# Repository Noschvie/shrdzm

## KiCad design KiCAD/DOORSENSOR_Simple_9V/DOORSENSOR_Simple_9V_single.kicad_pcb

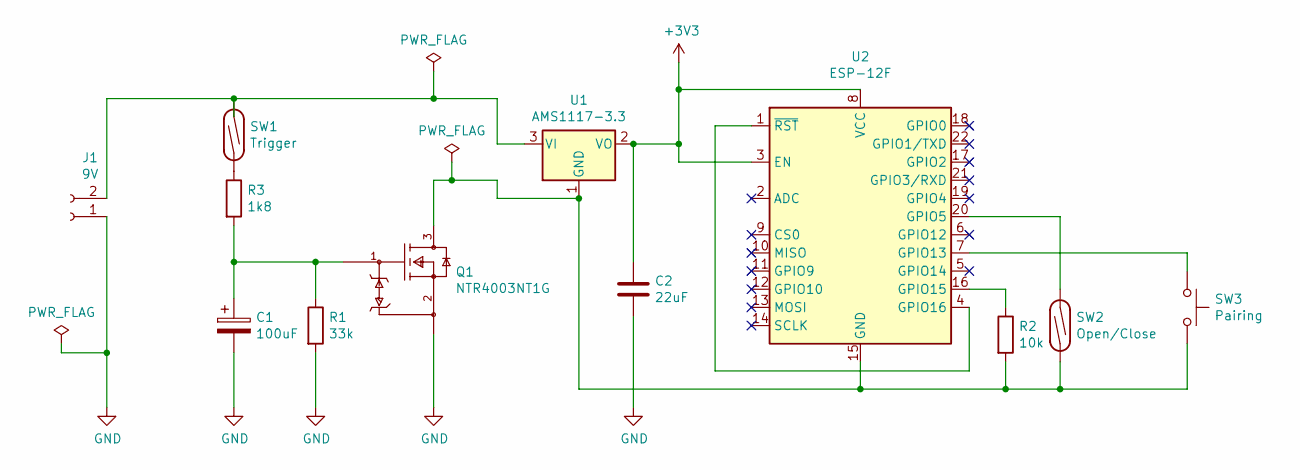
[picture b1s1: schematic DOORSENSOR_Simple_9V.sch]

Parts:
C1: 100uF; CP_Radial_D5.0mm_P2.50mm
C2: 22uF; C_1206_3216Metric_Pad1.33x1.80mm_HandSolder
J1: 9V; JST_PH_S2B-PH-K_1x02_P2.00mm_Horizontal
Q1: NTR4003NT1G; SOT-23; mouser part number 863-NTR4003NT1G; digikey description MOSFET N-CH 30V 500MA SOT-23
R1: 33k; R_0805_2012Metric_Pad1.20x1.40mm_HandSolder
R2: 10k; R_0805_2012Metric_Pad1.20x1.40mm_HandSolder
R3: 1k8; R_0805_2012Metric_Pad1.20x1.40mm_HandSolder
SW1: Trigger; Magnetic Reed Relay
SW2: Open/Close; Magnetic Reed Relay
SW3: Pairing; SW_SPST_CK_RS282G05A3
U1: AMS1117-3.3; SOT-223-3_TabPin2
U2: ESP-12F; ESP-12E

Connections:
+3V3: C2.1, U1.2 (VO), U2.3 (EN), U2.8 (VCC)
GND: C1.2, C2.2, J1.1, Q1.2 (S), R1.2
unnamed: C1.1, Q1.1 (G), R1.1, R3.2
unnamed: J1.2, SW1.1, U1.3 (VI)
unnamed: Q1.3 (D), R2.2, SW2.2, SW3.2, U1.1 (GND), U2.15 (GND)
unnamed: R2.1, U2.16 (GPIO15)
unnamed: R3.1, SW1.2
unnamed: SW2.1, U2.20 (GPIO5)
unnamed: SW3.1, U2.7 (GPIO13)
unnamed: U2.1 (~RST), U2.4 (GPIO16)

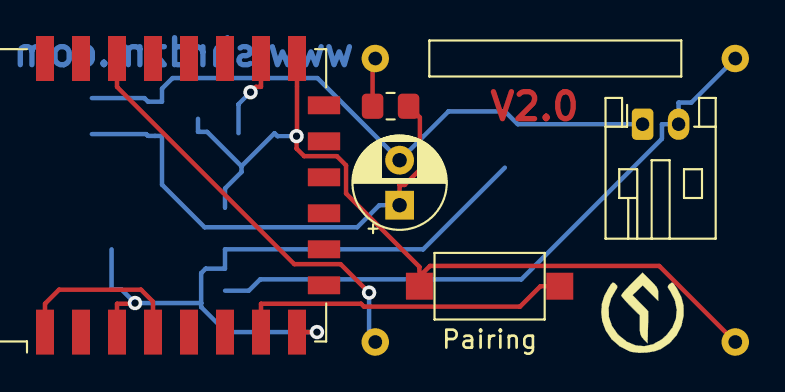
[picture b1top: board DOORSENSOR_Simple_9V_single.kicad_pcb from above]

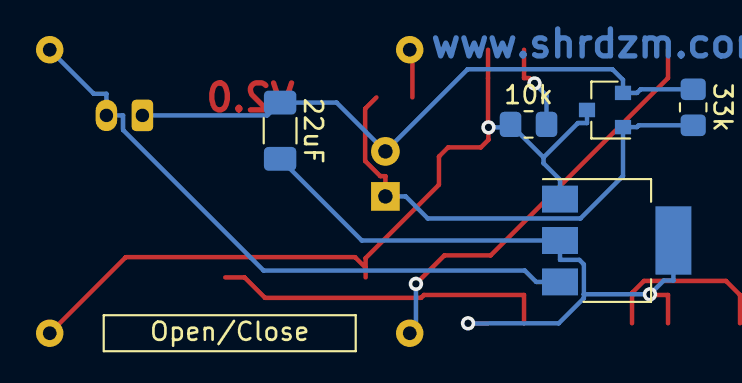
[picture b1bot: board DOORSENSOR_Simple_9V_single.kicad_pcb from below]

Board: 2 copper layers, 14 parts (7 on the bottom side), 10 nets.

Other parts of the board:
G1: LOGO; SHRDZM Symbol 5x5
G2: LOGO; SHRDZM 12x4

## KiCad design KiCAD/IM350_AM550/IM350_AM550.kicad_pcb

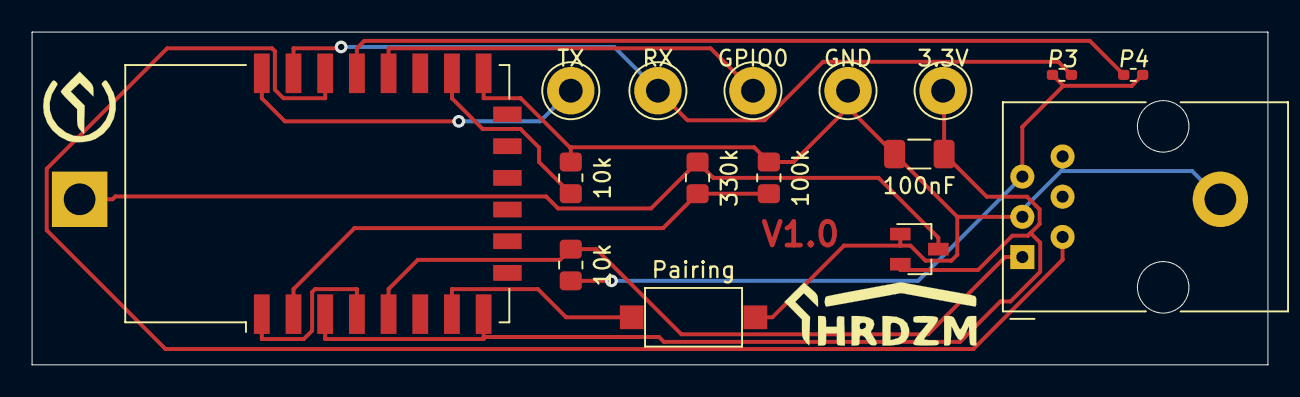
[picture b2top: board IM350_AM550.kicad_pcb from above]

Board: 2 copper layers, 78.0 x 21.0 mm, 19 parts (1 on the bottom side), 14 nets.

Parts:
BT1: Battery_Cell; BatteryHolder_MPD_BH-18650-PC2_NoHole
C2: 100nF; C_1206_3216Metric_Pad1.33x1.80mm_HandSolder
G1: LOGO; SHRDZM 12x4
G2: LOGO; SHRDZM Symbol 5x5
J1: 3.3V; Pin_D1.3mm_L11.0mm_LooseFit
J2: TX; Pin_D1.3mm_L11.0mm_LooseFit
J3: RX; Pin_D1.3mm_L11.0mm_LooseFit
J4: GPIO0; Pin_D1.3mm_L11.0mm_LooseFit
J6: GND; Pin_D1.3mm_L11.0mm_LooseFit
J7: RJ12; RJ12_Amphenol_54601
R1: 330k; R_0805_2012Metric_Pad1.20x1.40mm_HandSolder
R2: 100k; R_0805_2012Metric_Pad1.20x1.40mm_HandSolder
R3, R6: 0R; R_0402_1005Metric_Pad0.72x0.64mm_HandSolder
R4, R5: 10k; R_0805_2012Metric_Pad1.20x1.40mm_HandSolder
SW1: Pairing; SW_SPST_CK_RS282G05A3
U1: MCP1700-3302E_SOT23; SOT-23_Handsoldering
U2: ESP-12F; ESP-12E

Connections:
+3V3: C2.1, J1.1, U1.2, U2.3, U2.8
+3V8: BT1.1, R1.1, U1.3
/GPIO3: J3.1, R3.2, U2.21
/GPIO4: R6.2, U2.19
GND: BT1.2, C2.2, J6.1, J7.3, J7.6, R2.2, R4.2, SW1.2, U1.1, U2.15
unnamed: J2.1, U2.22
unnamed: J4.1, U2.18
unnamed: J7.1, R5.1, U2.5
unnamed: J7.2, U2.20
unnamed: J7.5, R3.1, R5.2, R6.1
unnamed: R1.2, R2.1, U2.2
unnamed: R4.1, U2.16
unnamed: SW1.1, U2.7
unnamed: U2.1, U2.4

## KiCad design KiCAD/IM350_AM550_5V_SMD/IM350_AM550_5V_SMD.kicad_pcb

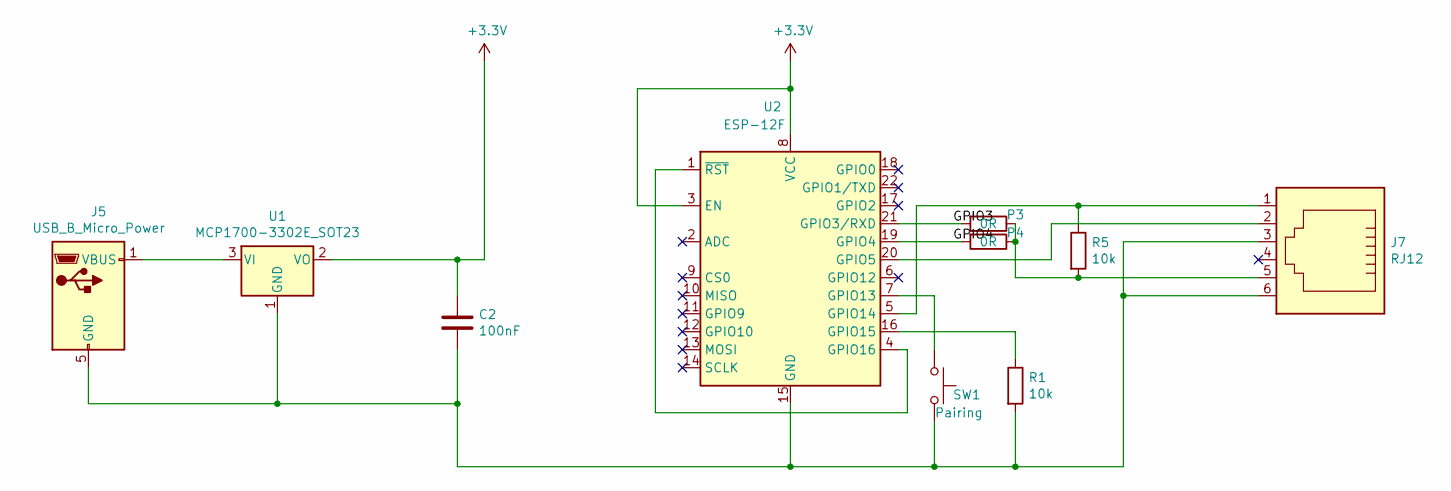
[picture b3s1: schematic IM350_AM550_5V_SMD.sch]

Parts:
C2: 100nF; C_1206_3216Metric_Pad1.33x1.80mm_HandSolder
J5: USB_B_Micro_Power; USB_Micro-B_Power
J7: RJ12; RJ12_Amphenol_54601_Reduced
P3, P4: 0R; R_0402_1005Metric_Pad0.72x0.64mm_HandSolder
R1, R5: 10k; R_0805_2012Metric_Pad1.20x1.40mm_HandSolder
SW1: Pairing; SW_SPST_CK_RS282G05A3
U1: MCP1700-3302E_SOT23; SOT-23_Handsoldering
U2: ESP-12F; ESP-12E

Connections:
+3V3: C2.1, U1.2 (VO), U2.3 (EN), U2.8 (VCC)
/GPIO3: P3.2, U2.21 (GPIO3/RXD)
/GPIO4: P4.2, U2.19 (GPIO4)
unnamed: C2.2, J5.5 (GND), J7.3, J7.6, R1.2, SW1.2, U1.1 (GND), U2.15 (GND)
unnamed: J5.1 (VBUS), U1.3 (VI)
unnamed: J7.1, R5.1, U2.5 (GPIO14)
unnamed: J7.2, U2.20 (GPIO5)
unnamed: J7.5, P3.1, P4.1, R5.2
unnamed: R1.1, U2.16 (GPIO15)
unnamed: SW1.1, U2.7 (GPIO13)
unnamed: U2.1 (~RST), U2.4 (GPIO16)

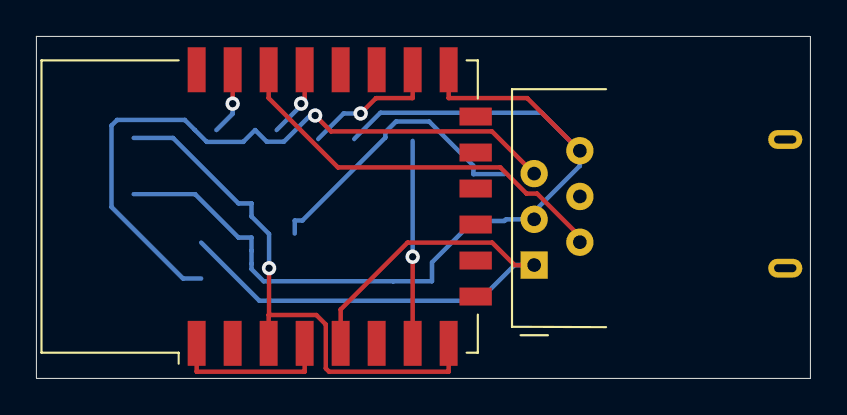
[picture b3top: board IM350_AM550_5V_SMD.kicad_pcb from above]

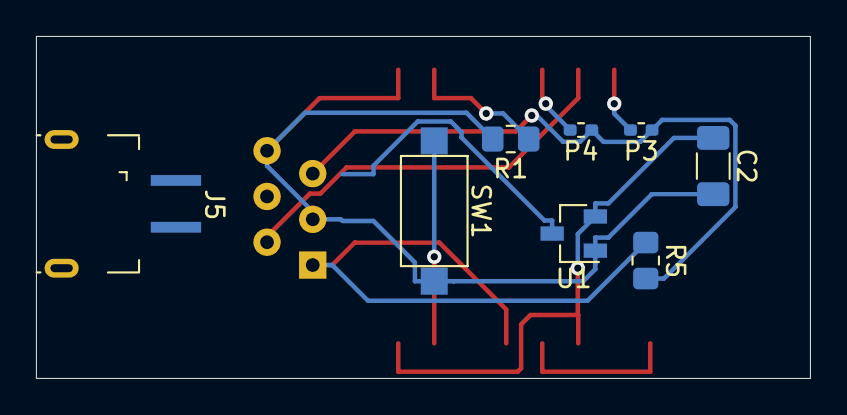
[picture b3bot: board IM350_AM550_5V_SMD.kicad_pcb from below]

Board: 2 copper layers, 43.0 x 19.0 mm, 10 parts (8 on the bottom side), 11 nets.
